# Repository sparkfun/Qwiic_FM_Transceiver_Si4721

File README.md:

# Qwiic FM Transceiver - Si4721

[*Qwiic FM Transceiver - Si4721 (SPX-15853)*](https://www.sparkfun.com/products/15853)

You're probably already familiar with Silicon Labs' brilliant 47xx line of radio devices. We've been carrying their FM tuners for a long time and find them reliable and simple to operate. That said, we thought it would be nice if you could _transmit_ as well as _receive_, so we looked into it and we found this excellent FM Transceiver!

The Si4721 integrates the complete tuner and transmit functions from previous Si47xx devices into one chip for both FM broadcast reception and standards-compliant*, unlicensed FM broadcast stereo transmission. On top of stereo audio the Si4721 will also transmit and receive RDS/RBDS, allowing you to send and receive strings of text on the FM Band. This is the same technology that modern commercial stations use to broadcast things like call signs and song names but we think you could have fun using it to broadcast sensor data or other arbitrary text data.

In order to be compliant with most broadcast regulations, this transmitter is extremely low power and has a reliable range of maybe 10 to 20 meters. These types of transmitters are most often found in things like intercoms or car stereo audio input adapters. Within range, however, the audio signal is extremely clear. 

The Qwiic FM Transceiver board includes not only the Si4721 IC but also a 3.5mm audio jack for line level input, a 3.5mm audio jack providing headphone level output via the on-board TPA6111 headphone amp, and a two position poke-home connector for easy antenna connection. The I²C address is jumper configurable between 0x11 and 0x63, allowing for multiple radio boards on a single Qwiic bus.

*In many parts of the world, using extremely low-power transmitters in the FM band for non-commercial purposes requires no license but you should always check the local laws just in case! <b>You are responsible for complying with local RF transmission regulations.
  
  Repository Contents
-------------------
* **/Hardware** - Eagle design files (.brd, .sch)

Documentation
--------------
* **[Arduino Radio Library](https://cdn.sparkfun.com/assets/f/2/a/3/6/Radio.zip)** - This is an archived (.zip) fork of the [Radio](https://github.com/mathertel/Radio) library with added Si4721 support and example code. 

License Information
-------------------

This product is _**open source**_! 

Please review the LICENSE.md file for license information. 

If you have any questions or concerns on licensing, please contact technical support through the [SparkFun forum](https://forum.sparkfun.com/index.php).

Please use, reuse, and modify these files as you see fit. Please maintain attribution to SparkFun Electronics and release any derivative under the same license.

Distributed as-is; no warranty is given.

- Your friends at SparkFun.

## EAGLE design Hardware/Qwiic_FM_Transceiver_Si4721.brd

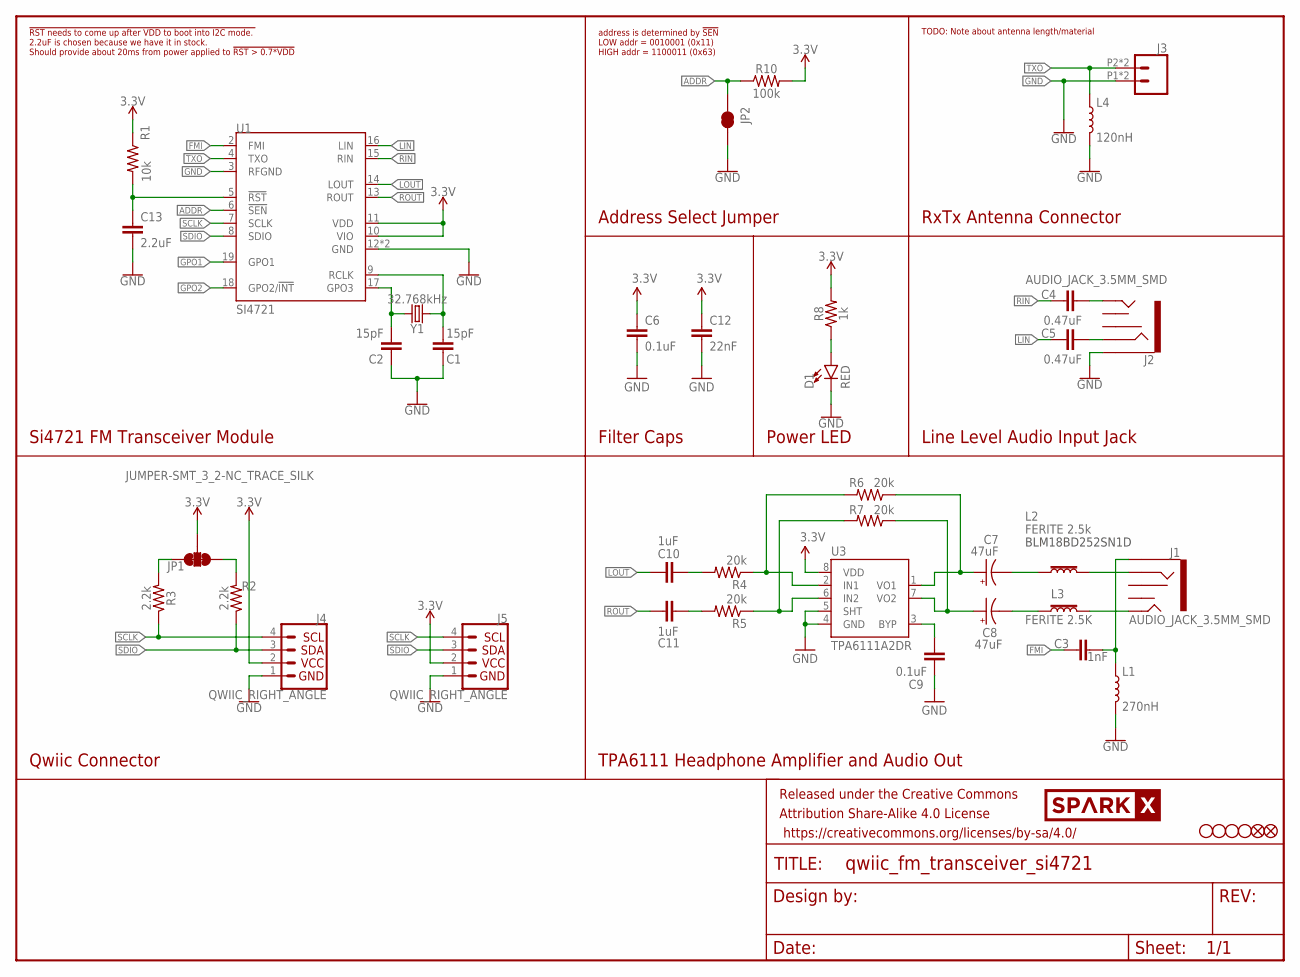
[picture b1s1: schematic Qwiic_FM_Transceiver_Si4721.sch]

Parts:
C1, C2: 15pF; 0603
C3: 1nF; 0603
C4, C5: 0.47uF; 0603
C6, C9: 0.1uF; 0603
C7, C8: 47uF; EIA3528
C10, C11: 1uF; 0603-CAP
C12: 22nF; 0603
C13: 2.2uF; 0603
D1: RED; LED-0603
FD1, FD2: FIDUCIAL0.2MM; FIDUCIAL-0.2MM
FRAME1: FRAME-LETTER; CREATIVE_COMMONS
H1, H2, H3, H4: STAND-OFF
J1, J2: AUDIO_JACK_3.5MM_SMD; AUDIO-JACK-3.5MM-SMD
J3: CONN_02SMALL_POKEHOME; 1X02_POKEHOME
J4, J5: QWIIC_RIGHT_ANGLE; JST04_1MM_RA
JP1: JUMPER-SMT_3_2-NC_TRACE_SILK; SMT-JUMPER_3_2-NC_TRACE_SILK
JP2: JUMPER-SMT_2_NC_TRACE_SILK; SMT-JUMPER_2_NC_TRACE_SILK
L1: 270nH; 0603
L2: FERITE 2.5k; 0603
L3: FERITE 2.5K; 0603
L4: 120nH; 0603
R1: 10k; 0603
R2, R3: 2.2k; 0603
R4, R5, R6, R7: 20k; 0603
R8: 1k; 0603
R10: 100k; 0603
U1: SI4721; QFN-20-3X3MM
U3: TPA6111A2DR; SO08
U$18: SPARKX-LOGO4; SPARKX-MEDIUM
Y1: 32.768kHz; CRYSTAL-SMD-3.2X1.5MM

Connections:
3.3V: C6.1, C12.1, J4.2, J5.2, JP1.2, R1.1, R8.2, R10.2, U1.10 (VIO), U1.11 (VDD), U3.8 (VDD)
ADDR: JP2.1, R10.1, U1.6 (!SEN)
FMI: C3.1, U1.2 (FMI)
GND: C1.1, C2.1, C6.2, C9.2, C12.2, C13.2, D1.C, J2.SLEEVE, J3.P1 (1), J3.P3 (1), J4.1, J5.1, JP2.2, L1.2, L4.2, U1.3 (RFGND), U1.12 (GND), U1.21 (GND), U3.4 (GND), U3.5 (SHT)
GPO1: U1.19 (GPO1)
GPO2: U1.18 (GPO2/!INT)
LIN: C5.1, U1.16 (LIN)
LOUT: C10.1, U1.14 (LOUT)
unnamed: C13.1, R1.2, U1.5 (!RST)
unnamed: C1.2, U1.9 (RCLK), Y1.P$1 (1)
unnamed: J1.RING, L2.2
unnamed: J1.TIP, L3.2
unnamed: C3.2, J1.SLEEVE, L1.1
unnamed: C4.2, J2.TIP
unnamed: C7.A (+), R6.1, U3.1 (VO1)
unnamed: C2.2, U1.17 (GPO3), Y1.P$2 (2)
unnamed: C8.A (+), R7.1, U3.7 (VO2)
unnamed: C9.1, U3.3 (BYP)
unnamed: R4.1, R6.2, U3.2 (IN1)
unnamed: R5.1, R7.2, U3.6 (IN2)
unnamed: C10.2, R4.2
unnamed: C11.2, R5.2
unnamed: C7.C (-), L2.1
unnamed: C8.C (-), L3.1
unnamed: C5.2, J2.RING
unnamed: JP1.3, R2.2
unnamed: JP1.1, R3.2
unnamed: D1.A, R8.1
RIN: C4.1, U1.15 (RIN)
ROUT: C11.1, U1.13 (ROUT)
SCLK: J4.4, J5.4, R3.1, U1.7 (SCLK)
SDIO: J4.3, J5.3, R2.1, U1.8 (SDIO)
TXO: J3.P2 (2), J3.P4 (2), L4.1, U1.4 (TXO)

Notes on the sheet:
BLM18BD252SN1D
Si4721 FM Transceiver Module
Address Select Jumper
Power LED
Line Level Audio Input Jack
RxTx Antenna Connector
Qwiic Connector
TPA6111 Headphone Amplifier and Audio Out
Filter Caps
address is determined by !SEN LOW addr = 0010001 (0x11) HIGH addr = 1100011 (0x63)
TODO: Note about antenna length/material
!RST needs to come up after VDD to boot into I2C mode. 2.2uF is chosen because we have it in stock. Should provide about 20ms from power applied to !RST > 0.7*VDD

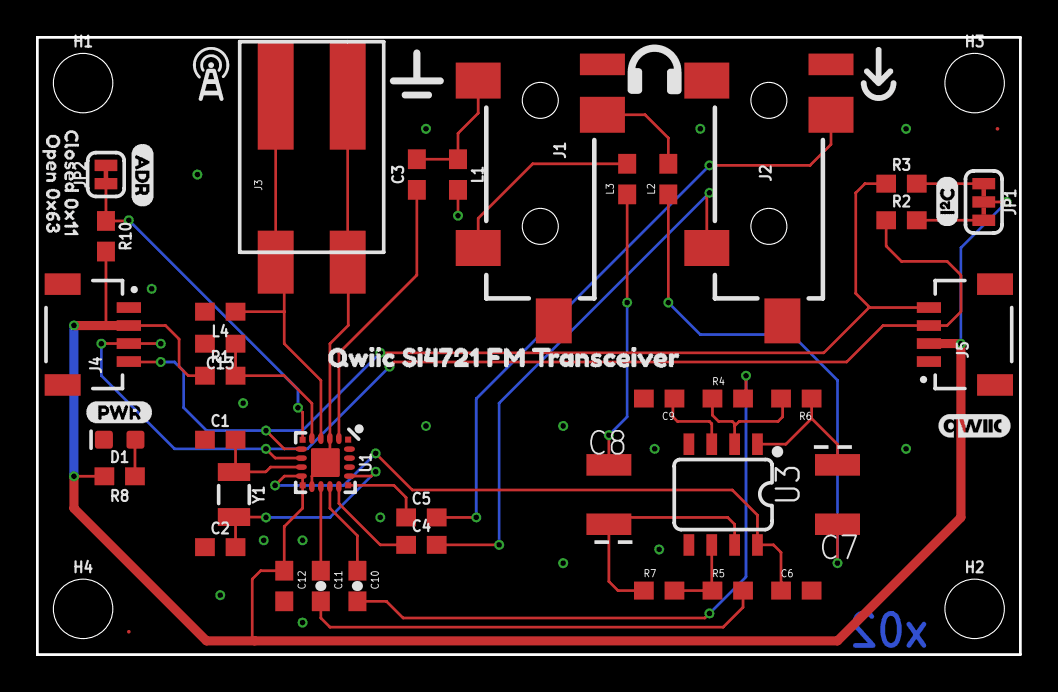
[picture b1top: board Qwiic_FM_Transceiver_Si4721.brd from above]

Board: 2 copper layers, 54.6 x 34.3 mm, 62 parts (7 on the bottom side), 31 nets.

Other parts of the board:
U$1, U$2: QWIIC_SI4721_FM_TRANSCEIVER0
U$3: QWIIC_4MM
U$4: ANTENNA1
U$5: PWR-()-03
U$6: OSHW-LOGO-S
U$7: GND0
U$8: LINE_IN2
U$9: PHONES_OUT3
U$10: PHONES#PNG
U$11: IN#PNG
U$12: GND#PNG
U$13: ANTENNA#PNG
U$14: I_SUPER2_C-()-03
U$15: CLOSED_0X110
U$16: ADR-()-03
U$17: OPEN_0X631

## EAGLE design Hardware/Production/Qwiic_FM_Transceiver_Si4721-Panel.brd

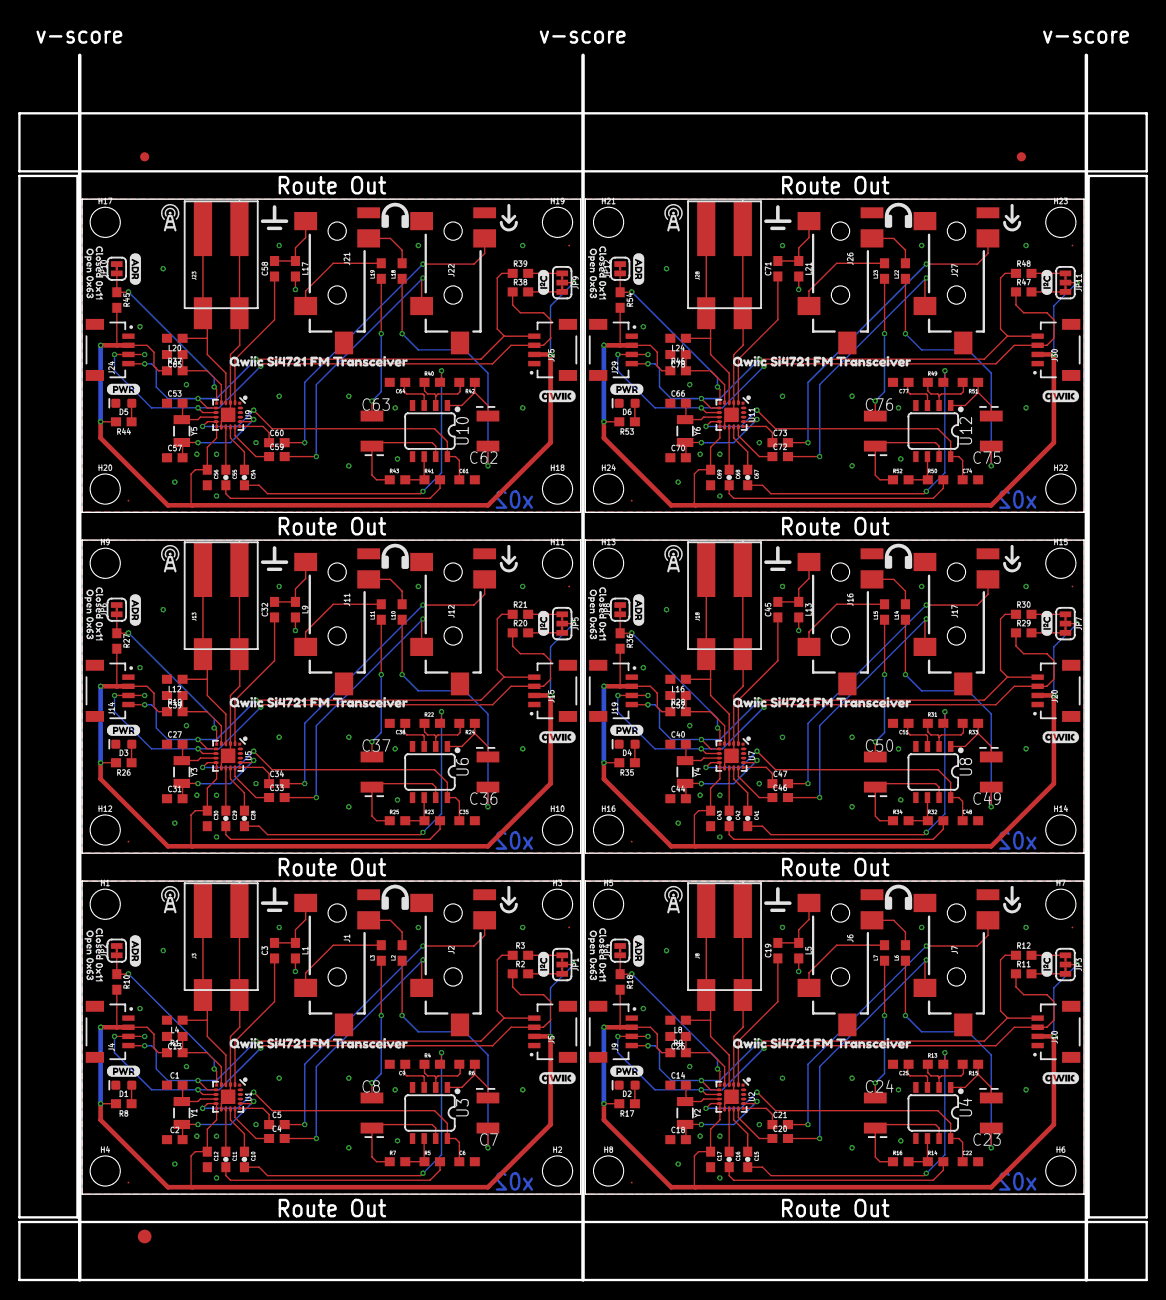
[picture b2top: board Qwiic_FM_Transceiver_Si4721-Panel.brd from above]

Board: 2 copper layers, 123.4 x 134.1 mm, 369 parts (42 on the bottom side), 186 nets.

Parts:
C1, C2, C14, C18, C27, C31, C40, C44, C53, C57, C66, C70: 15pF; 0603
C3, C19, C32, C45, C58, C71: 1nF; 0603
C4, C5, C20, C21, C33, C34, C46, C47, C59, C60, C72, C73: 0.47uF; 0603
C6, C9, C22, C25, C35, C38, C48, C51, C61, C64, C74, C77: 0.1uF; 0603
C7, C8, C23, C24, C36, C37, C49, C50, C62, C63, C75, C76: 47uF; EIA3528
C10, C11, C15, C16, C28, C29, C41, C42, C54, C55, C67, C68: 1uF; 0603-CAP
C12, C17, C30, C43, C56, C69: 22nF; 0603
C13, C26, C39, C52, C65, C78: 2.2uF; 0603
D1, D2, D3, D4, D5, D6: RED; LED-0603
E$1, E$2: FIDUCIAL-1X2
E$3: FIDUCIAL-1.5X3
FD1, FD2, FD3, FD4, FD5, FD6, FD7, FD8, FD9, FD10, FD11, FD12: FIDUCIAL0.2MM; FIDUCIAL-0.2MM
H1, H2, H3, H4, H5, H6, H7, H8, H9, H10, H11, H12, H13, H14, H15, H16, H17, H18, H19, H20, H21, H22, H23, H24: STAND-OFF
J1, J2, J6, J7, J11, J12, J16, J17, J21, J22, J26, J27: AUDIO_JACK_3.5MM_SMD; AUDIO-JACK-3.5MM-SMD
J3, J8, J13, J18, J23, J28: 1X02_POKEHOME
J4, J5, J9, J10, J14, J15, J19, J20, J24, J25, J29, J30: QWIIC_RIGHT_ANGLE; JST04_1MM_RA
JP1, JP3, JP5, JP7, JP9, JP11: JUMPER-SMT_3_2-NC_TRACE_SILK; SMT-JUMPER_3_2-NC_TRACE_SILK
JP2, JP4, JP6, JP8, JP10, JP12: SMT-JUMPER_2_NC_TRACE_SILK
L1, L5, L9, L13, L17, L21: 270nH; 0603
L2, L6, L10, L14, L18, L22: FERITE 2.5k; 0603
L3, L7, L11, L15, L19, L23: FERITE 2.5K; 0603
L4, L8, L12, L16, L20, L24: 120nH; 0603
R1, R9, R19, R28, R37, R46: 10k; 0603
R2, R3, R11, R12, R20, R21, R29, R30, R38, R39, R47, R48: 2.2k; 0603
R4, R5, R6, R7, R13, R14, R15, R16, R22, R23, R24, R25, R31, R32, R33, R34, R40, R41, R42, R43, R49, R50, R51, R52: 20k; 0603
R8, R17, R26, R35, R44, R53: 1k; 0603
R10, R18, R27, R36, R45, R54: 100k; 0603
U1, U2, U5, U7, U9, U11: SI4721; QFN-20-3X3MM
U3, U4, U6, U8, U10, U12: TPA6111A2DR; SO08
U$1, U$2, U$19, U$31, U$37, U$49, U$55, U$67, U$73, U$85, U$91, U$103: QWIIC_SI4721_FM_TRANSCEIVER0
U$3, U$20, U$38, U$56, U$74, U$92: QWIIC_4MM
U$4, U$22, U$40, U$58, U$76, U$94: ANTENNA1
U$5, U$32, U$50, U$68, U$86, U$104: PWR-()-03
U$6, U$21, U$39, U$57, U$75, U$93: OSHW-LOGO-S
U$7, U$23, U$41, U$59, U$77, U$95: GND0
U$8, U$24, U$42, U$60, U$78, U$96: LINE_IN2
U$9, U$25, U$43, U$61, U$79, U$97: PHONES_OUT3
U$10, U$26, U$44, U$62, U$80, U$98: PHONES#PNG
U$11, U$27, U$45, U$63, U$81, U$99: IN#PNG
U$12, U$28, U$46, U$64, U$82, U$100: GND#PNG
U$13, U$29, U$47, U$65, U$83, U$101: ANTENNA#PNG
U$14, U$33, U$51, U$69, U$87, U$105: I_SUPER2_C-()-03
U$15, U$35, U$53, U$71, U$89, U$107: CLOSED_0X110
U$16, U$34, U$52, U$70, U$88, U$106: ADR-()-03
U$17, U$36, U$54, U$72, U$90, U$108: OPEN_0X631
U$18, U$30, U$48, U$66, U$84, U$102: SPARKX-LOGO4; SPARKX-MEDIUM
Y1, Y2, Y3, Y4, Y5, Y6: 32.768kHz; CRYSTAL-SMD-3.2X1.5MM

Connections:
3.3V: C6.1, C12.1, J4.2, J5.2, JP1.2, R1.1, R8.2, R10.2, U1.10, U1.11, U3.8
3.3V1: C17.1, C22.1, J9.2, J10.2, JP3.2, R9.1, R17.2, R18.2, U2.10, U2.11, U4.8
3.3V2: C30.1, C35.1, J14.2, J15.2, JP5.2, R19.1, R26.2, R27.2, U5.10, U5.11, U6.8
3.3V3: C43.1, C48.1, J19.2, J20.2, JP7.2, R28.1, R35.2, R36.2, U7.10, U7.11, U8.8
3.3V4: C56.1, C61.1, J24.2, J25.2, JP9.2, R37.1, R44.2, R45.2, U9.10, U9.11, U10.8
3.3V5: C69.1, C74.1, J29.2, J30.2, JP11.2, R46.1, R53.2, R54.2, U11.10, U11.11, U12.8
ADDR: JP2.1, R10.1, U1.6
ADDR1: JP4.1, R18.1, U2.6
ADDR2: JP6.1, R27.1, U5.6
ADDR3: JP8.1, R36.1, U7.6
ADDR4: JP10.1, R45.1, U9.6
ADDR5: JP12.1, R54.1, U11.6
FMI: C3.1, U1.2
FMI1: C19.1, U2.2
FMI2: C32.1, U5.2
FMI3: C45.1, U7.2
FMI4: C58.1, U9.2
FMI5: C71.1, U11.2
GND: C1.1, C2.1, C6.2, C9.2, C12.2, C13.2, D1.C, J2.SLEEVE, J3.P1, J3.P3, J4.1, J5.1, JP2.2, L1.2, L4.2, U1.3, U1.12, U1.21, U3.4, U3.5
GND1: C14.1, C17.2, C18.1, C22.2, C25.2, C26.2, D2.C, J7.SLEEVE, J8.P1, J8.P3, J9.1, J10.1, JP4.2, L5.2, L8.2, U2.3, U2.12, U2.21, U4.4, U4.5
GND2: C27.1, C30.2, C31.1, C35.2, C38.2, C39.2, D3.C, J12.SLEEVE, J13.P1, J13.P3, J14.1, J15.1, JP6.2, L9.2, L12.2, U5.3, U5.12, U5.21, U6.4, U6.5
GND3: C40.1, C43.2, C44.1, C48.2, C51.2, C52.2, D4.C, J17.SLEEVE, J18.P1, J18.P3, J19.1, J20.1, JP8.2, L13.2, L16.2, U7.3, U7.12, U7.21, U8.4, U8.5
GND4: C53.1, C56.2, C57.1, C61.2, C64.2, C65.2, D5.C, J22.SLEEVE, J23.P1, J23.P3, J24.1, J25.1, JP10.2, L17.2, L20.2, U9.3, U9.12, U9.21, U10.4, U10.5
GND5: C66.1, C69.2, C70.1, C74.2, C77.2, C78.2, D6.C, J27.SLEEVE, J28.P1, J28.P3, J29.1, J30.1, JP12.2, L21.2, L24.2, U11.3, U11.12, U11.21, U12.4, U12.5
LIN: C5.1, U1.16
LIN1: C21.1, U2.16
LIN2: C34.1, U5.16
LIN3: C47.1, U7.16
LIN4: C60.1, U9.16
LIN5: C73.1, U11.16
LOUT: C10.1, U1.14
LOUT1: C15.1, U2.14
LOUT2: C28.1, U5.14
LOUT3: C41.1, U7.14
LOUT4: C54.1, U9.14
LOUT5: C67.1, U11.14
unnamed: C13.1, R1.2, U1.5
unnamed: C1.2, U1.9, Y1.P$1
unnamed: J1.RING, L2.2
unnamed: J1.TIP, L3.2
unnamed: C3.2, J1.SLEEVE, L1.1
unnamed: C4.2, J2.TIP
unnamed: C7.A, R6.1, U3.1
unnamed: C2.2, U1.17, Y1.P$2
unnamed: C8.A, R7.1, U3.7
unnamed: C9.1, U3.3
unnamed: R4.1, R6.2, U3.2
unnamed: R5.1, R7.2, U3.6
unnamed: C10.2, R4.2
unnamed: C11.2, R5.2
unnamed: C7.C, L2.1
unnamed: C8.C, L3.1
unnamed: C5.2, J2.RING
unnamed: JP1.3, R2.2
unnamed: JP1.1, R3.2
unnamed: D1.A, R8.1
unnamed: C14.2, U2.9, Y2.P$1
unnamed: C18.2, U2.17, Y2.P$2
unnamed: C26.1, R9.2, U2.5
unnamed: C19.2, J6.SLEEVE, L5.1
unnamed: C23.A, R15.1, U4.1
unnamed: C24.A, R16.1, U4.7
unnamed: C25.1, U4.3
unnamed: R13.1, R15.2, U4.2
unnamed: R14.1, R16.2, U4.6
unnamed: C15.2, R13.2
unnamed: C16.2, R14.2
unnamed: C23.C, L6.1
unnamed: C24.C, L7.1
unnamed: J6.RING, L6.2
unnamed: J6.TIP, L7.2
unnamed: C20.2, J7.TIP
unnamed: C21.2, J7.RING
unnamed: JP3.3, R11.2
unnamed: JP3.1, R12.2
unnamed: D2.A, R17.1
unnamed: C27.2, U5.9, Y3.P$1
unnamed: C31.2, U5.17, Y3.P$2
unnamed: C39.1, R19.2, U5.5
unnamed: C32.2, J11.SLEEVE, L9.1
unnamed: C36.A, R24.1, U6.1
unnamed: C37.A, R25.1, U6.7
unnamed: C38.1, U6.3
unnamed: R22.1, R24.2, U6.2
unnamed: R23.1, R25.2, U6.6
unnamed: C28.2, R22.2
unnamed: C29.2, R23.2
unnamed: C36.C, L10.1
unnamed: C37.C, L11.1
unnamed: J11.RING, L10.2
unnamed: J11.TIP, L11.2
unnamed: C33.2, J12.TIP
unnamed: C34.2, J12.RING
unnamed: JP5.3, R20.2
unnamed: JP5.1, R21.2
unnamed: D3.A, R26.1
unnamed: C40.2, U7.9, Y4.P$1
unnamed: C44.2, U7.17, Y4.P$2
unnamed: C52.1, R28.2, U7.5
unnamed: C45.2, J16.SLEEVE, L13.1
unnamed: C49.A, R33.1, U8.1
unnamed: C50.A, R34.1, U8.7
unnamed: C51.1, U8.3
unnamed: R31.1, R33.2, U8.2
unnamed: R32.1, R34.2, U8.6
unnamed: C41.2, R31.2
unnamed: C42.2, R32.2
unnamed: C49.C, L14.1
unnamed: C50.C, L15.1
unnamed: J16.RING, L14.2
unnamed: J16.TIP, L15.2
unnamed: C46.2, J17.TIP
unnamed: C47.2, J17.RING
unnamed: JP7.3, R29.2
unnamed: JP7.1, R30.2
unnamed: D4.A, R35.1
unnamed: C53.2, U9.9, Y5.P$1
unnamed: C57.2, U9.17, Y5.P$2
unnamed: C65.1, R37.2, U9.5
unnamed: C58.2, J21.SLEEVE, L17.1
unnamed: C62.A, R42.1, U10.1
unnamed: C63.A, R43.1, U10.7
unnamed: C64.1, U10.3
unnamed: R40.1, R42.2, U10.2
unnamed: R41.1, R43.2, U10.6
unnamed: C54.2, R40.2
unnamed: C55.2, R41.2
unnamed: C62.C, L18.1
unnamed: C63.C, L19.1
unnamed: J21.RING, L18.2
unnamed: J21.TIP, L19.2
unnamed: C59.2, J22.TIP
unnamed: C60.2, J22.RING
unnamed: JP9.3, R38.2
unnamed: JP9.1, R39.2
unnamed: D5.A, R44.1
unnamed: C66.2, U11.9, Y6.P$1
unnamed: C70.2, U11.17, Y6.P$2
unnamed: C78.1, R46.2, U11.5
unnamed: C71.2, J26.SLEEVE, L21.1
unnamed: C75.A, R51.1, U12.1
unnamed: C76.A, R52.1, U12.7
unnamed: C77.1, U12.3
unnamed: R49.1, R51.2, U12.2
unnamed: R50.1, R52.2, U12.6
unnamed: C67.2, R49.2
unnamed: C68.2, R50.2
unnamed: C75.C, L22.1
unnamed: C76.C, L23.1
unnamed: J26.RING, L22.2
unnamed: J26.TIP, L23.2
unnamed: C72.2, J27.TIP
unnamed: C73.2, J27.RING
unnamed: JP11.3, R47.2
unnamed: JP11.1, R48.2
unnamed: D6.A, R53.1
RIN: C4.1, U1.15
RIN1: C20.1, U2.15
RIN2: C33.1, U5.15
RIN3: C46.1, U7.15
RIN4: C59.1, U9.15
RIN5: C72.1, U11.15
ROUT: C11.1, U1.13
ROUT1: C16.1, U2.13
ROUT2: C29.1, U5.13
ROUT3: C42.1, U7.13
ROUT4: C55.1, U9.13
ROUT5: C68.1, U11.13
SCLK: J4.4, J5.4, R3.1, U1.7
SCLK1: J9.4, J10.4, R12.1, U2.7
SCLK2: J14.4, J15.4, R21.1, U5.7
SCLK3: J19.4, J20.4, R30.1, U7.7
SCLK4: J24.4, J25.4, R39.1, U9.7
SCLK5: J29.4, J30.4, R48.1, U11.7
SDIO: J4.3, J5.3, R2.1, U1.8
SDIO1: J9.3, J10.3, R11.1, U2.8
SDIO2: J14.3, J15.3, R20.1, U5.8
SDIO3: J19.3, J20.3, R29.1, U7.8
SDIO4: J24.3, J25.3, R38.1, U9.8
SDIO5: J29.3, J30.3, R47.1, U11.8
TXO: J3.P2, J3.P4, L4.1, U1.4
TXO1: J8.P2, J8.P4, L8.1, U2.4
TXO2: J13.P2, J13.P4, L12.1, U5.4
TXO3: J18.P2, J18.P4, L16.1, U7.4
TXO4: J23.P2, J23.P4, L20.1, U9.4
TXO5: J28.P2, J28.P4, L24.1, U11.4

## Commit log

2019-09-26 Finished Schematic
2019-09-27 x01
    x01
2019-09-27 x01 protos ordered
2019-11-01 x02 hardware order
2019-12-11 Production panels
2019-12-11 Clean-up
    Deleting unneccessary files and rearranging to make the repo presentable

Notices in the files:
parts and their libraries:
SparkFun-Capacitors: Licensing: Creative Commons ShareAlike 4.0 International - https://creativecommons.org/licenses/by-sa/4.0
SparkFun-Aesthetics: Released under the Creative Commons Attribution Share-Alike 4.0 License
SparkFun-Aesthetics: https://creativecommons.org/licenses/by-sa/4.0
